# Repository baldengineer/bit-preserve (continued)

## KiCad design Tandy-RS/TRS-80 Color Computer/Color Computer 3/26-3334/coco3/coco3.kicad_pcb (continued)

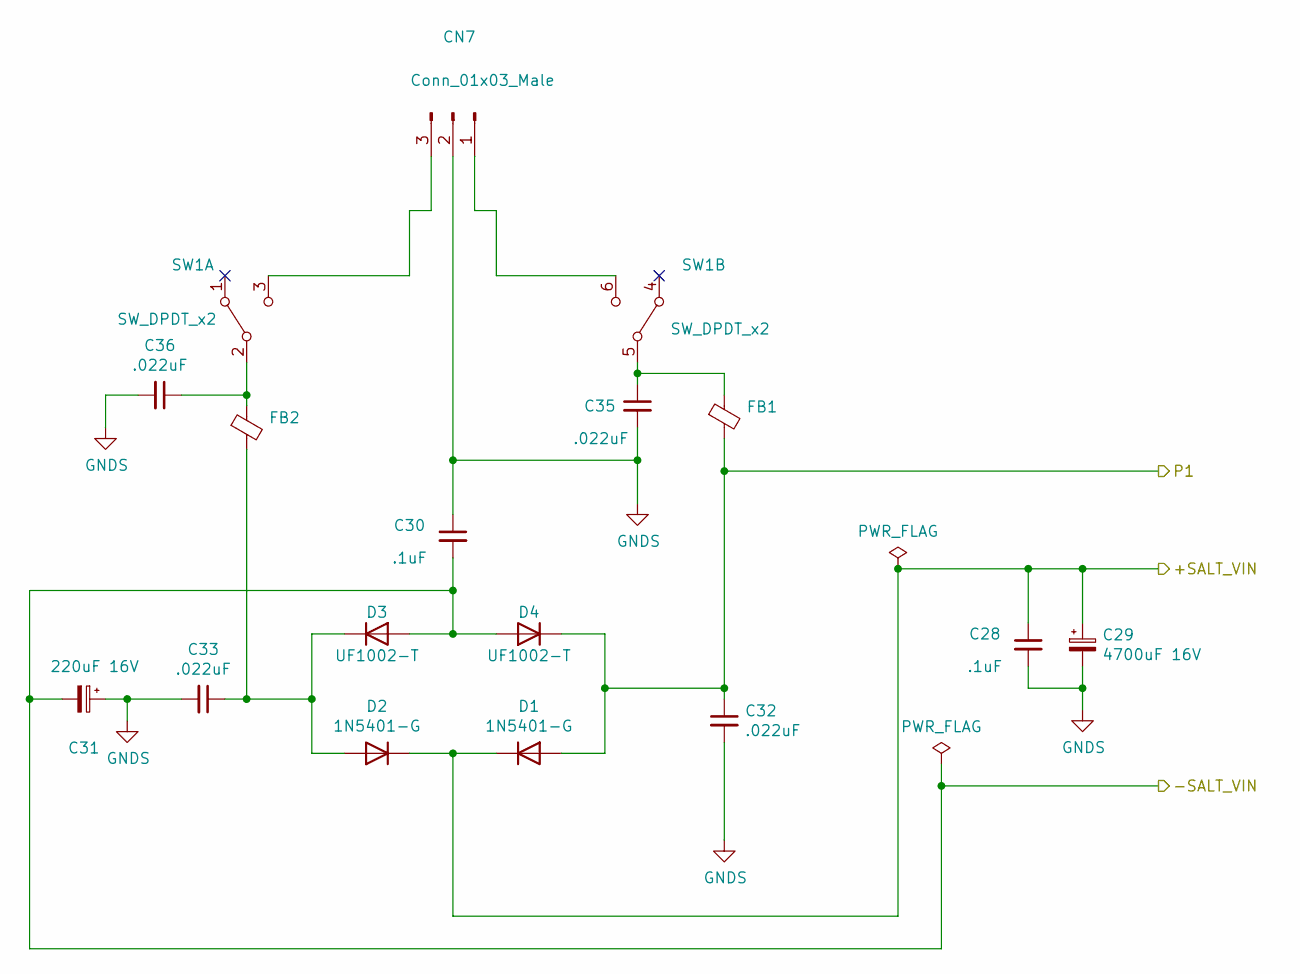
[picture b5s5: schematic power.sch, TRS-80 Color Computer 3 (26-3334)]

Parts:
C28, C30: .1uF; C_Disc_D4.7mm_W2.5mm_P5.00mm; Manufacturer part# FG28C0G1H103JNT06
C29: 4700uF 16V; CP_Radial_D12.5mm_P5.00mm; Manufacturer part# 16PK4700MEFC12.5X25
C31: 220uF 16V; CP_Radial_D8.0mm_P5.00mm; Manufacturer part# URS1C221MPD1TA
C32, C33, C35, C36: .022uF; C_Disc_D8.0mm_W2.5mm_P5.00mm; Manufacturer part# C317C223M5U5TA7301
CN7: Conn_01x03_Male; Molex_KK-396_A-41791-0003_1x03_P3.96mm_Vertical; Manufacturer part# 0009652038
D1, D2: 1N5401-G; D_DO-201AD_P15.24mm_Horizontal; Manufacturer part# 1N5401
D3, D4: UF1002-T; D_DO-41_SOD81_P10.16mm_Horizontal; Manufacturer part# UF1002-T
FB1, FB2: FB_28L0138-10R-10; Manufacturer part# 28L0138-10R-10
SW1: SW_DPDT_x2; F2UEE; Manufacturer part# F2UEE

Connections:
/peripherals/+SALT_VIN: C28.1, C29.1, D1.1 (K), D2.1 (K); also elsewhere on the board
/peripherals/-SALT_VIN: C30.2, C31.2, D3.2 (A), D4.2 (A); also elsewhere on the board
/power/P1: C32.1, D1.2 (A), D4.1 (K), FB1.2; also elsewhere on the board
GNDS: C28.2, C29.2, C30.1, C31.1, C32.2, C33.2, C35.2, C36.2, CN7.2; also elsewhere on the board
unnamed: C33.1, D2.2 (A), D3.1 (K), FB2.2
unnamed: C35.1, FB1.1, SW1.5 (B)
unnamed: C36.1, FB2.1, SW1.2 (B)
unnamed: CN7.1, SW1.6 (C)
unnamed: CN7.3, SW1.3 (C)

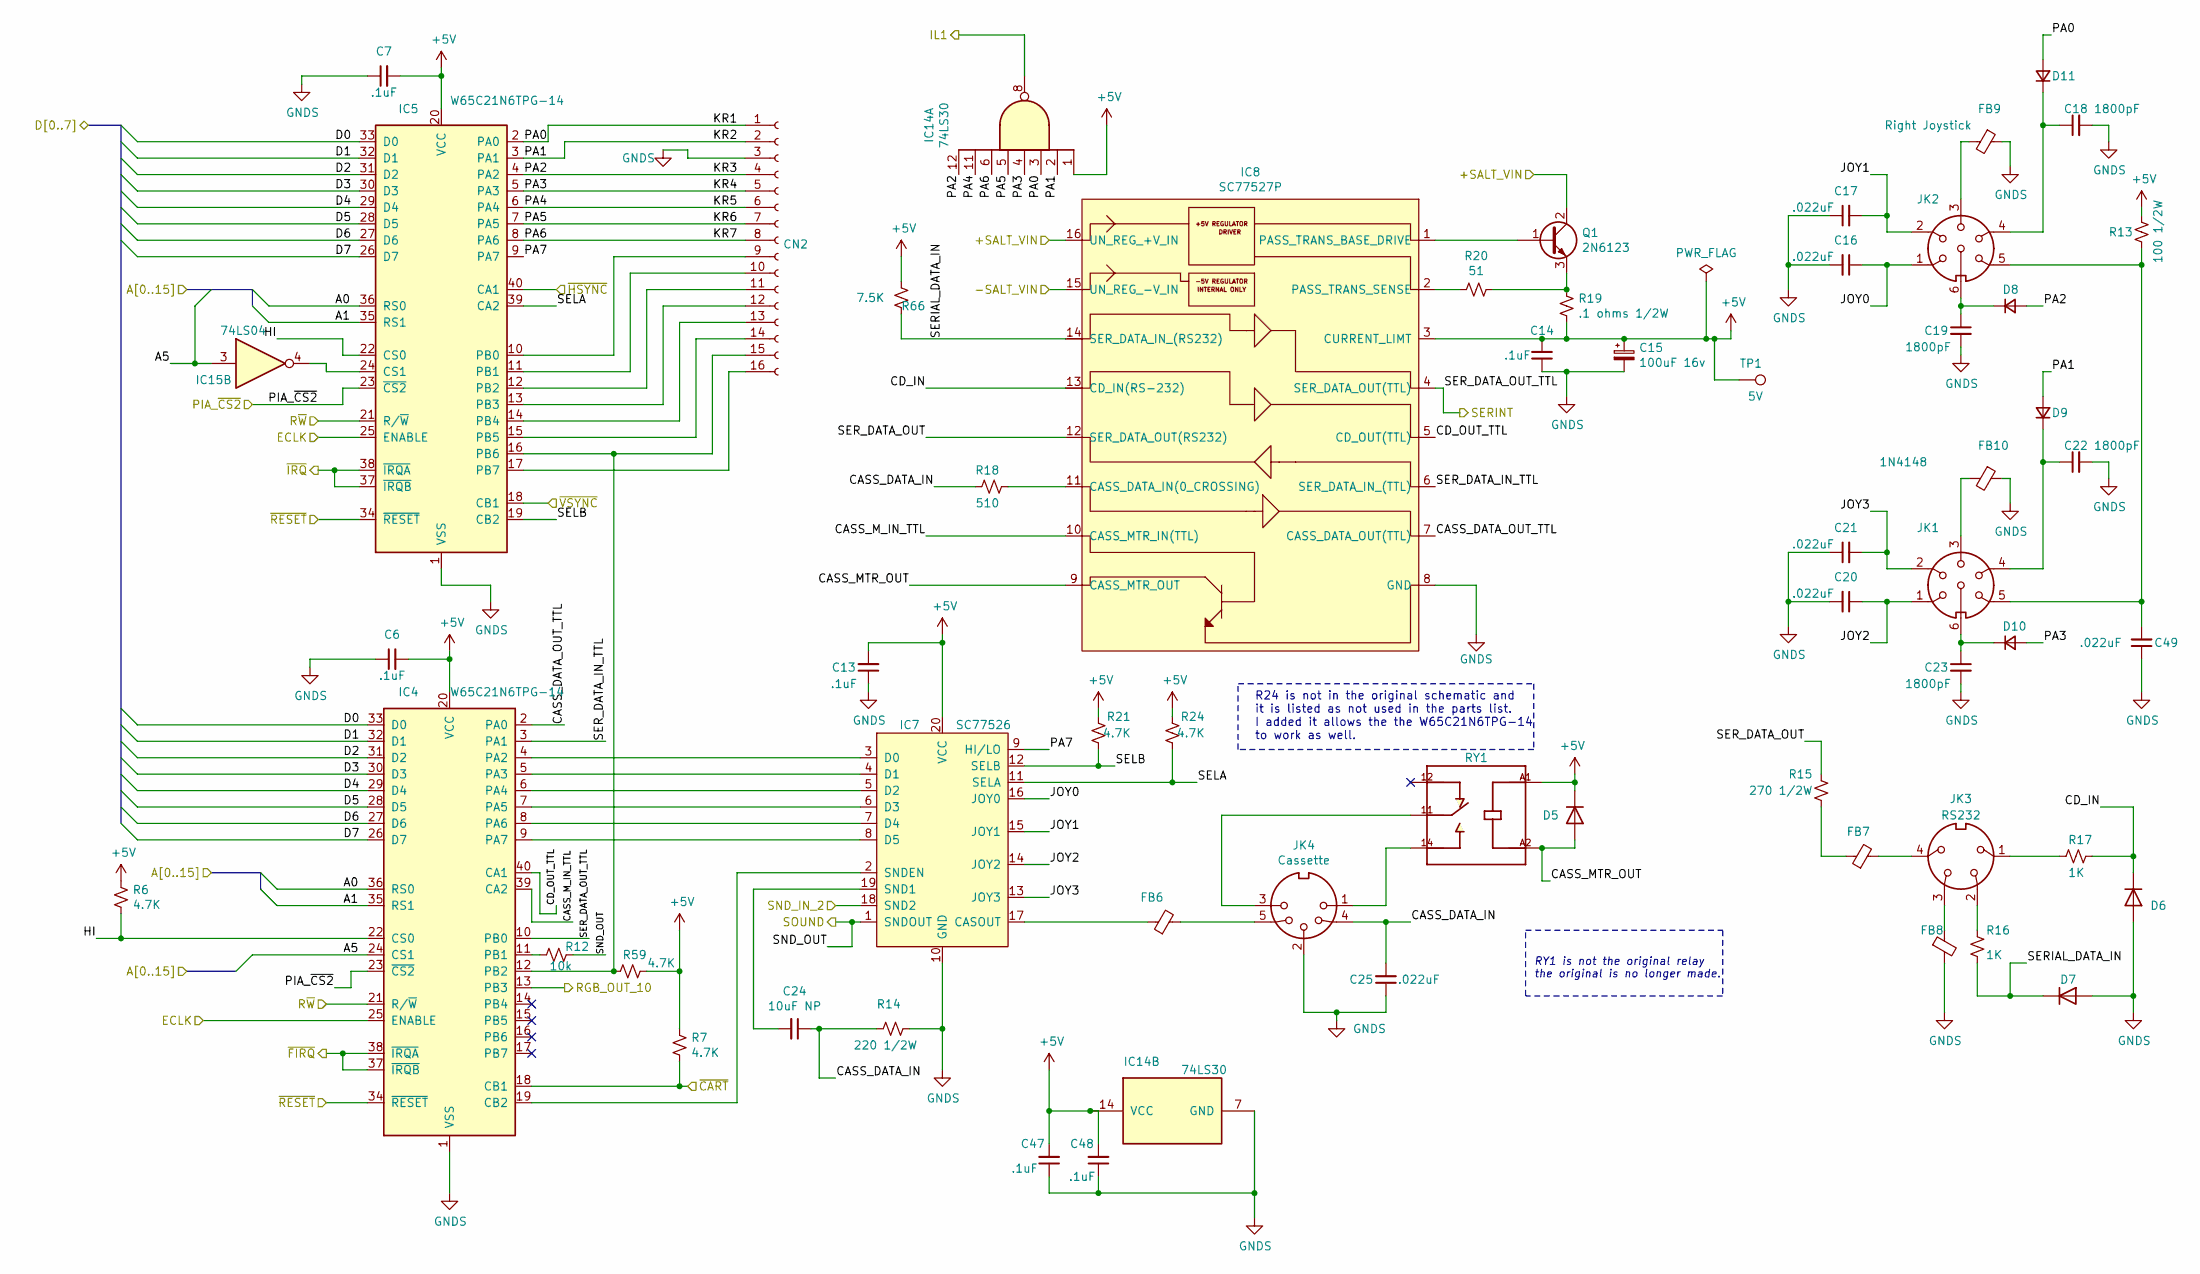
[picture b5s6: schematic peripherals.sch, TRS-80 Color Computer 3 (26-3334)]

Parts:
C6, C7, C13, C14, C47, C48: .1uF; C_Disc_D4.7mm_W2.5mm_P5.00mm; Manufacturer part# FG28C0G1H103JNT06
C15: 100uF 16v; CP_Radial_D8.0mm_P5.00mm; Manufacturer part# UST1C101MDD1TA
C16, C17, C20, C21, C25, C49: .022uF; C_Disc_D8.0mm_W2.5mm_P5.00mm; Manufacturer part# C317C223M5U5TA7301
C18, C19, C22, C23: 1800pF; C_Disc_D4.7mm_W2.5mm_P5.00mm; Manufacturer part# FA28C0G1H182JNU06
C24: 10uF NP; C_Radial_D6.3mm_H5.0mm_P2.50mm; Manufacturer part# UVP1E100MDD1TD
CN2: Conn_01x16_Female; PinHeader_1x16_P2.54mm_Vertical; Manufacturer part# 6-520415-6
D5: 1N4148; D_DO-35_SOD27_P7.62mm_Horizontal; Manufacturer part# 1N4148
D6, D7: 1N5228B-TAP; D_DO-35_SOD27_P7.62mm_Horizontal; Manufacturer part# 1N5228B-TAP
D8, D9, D10, D11: 1N4148; CUI_SDS-60J; Manufacturer part# DIODE GEN PURP 100V 200MA DO35
FB6, FB7, FB8, FB9, FB10: FB_28L0138-10R-10; Manufacturer part# 28L0138-10R-10
IC4, IC5: W65C21N6TPG-14; DIP-40_W15.24mm_Socket; Manufacturer part# W65C21N6TPG-14
IC7: SC77526; DIP-20_W7.62mm_Socket; Manufacturer part# 243-20-1-03
IC8: SC77527P; DIP-16_W7.62mm_Socket; Manufacturer part# 1-2199298-4
IC14: 74LS30; DIP-14_W7.62mm_Socket; Manufacturer part# SN74LS30N
IC15: 74LS04; DIP-14_W7.62mm_Socket; Manufacturer part# SN74LS04N
JK1: 1N4148; CUI_SDS-60J; Manufacturer part# 1N4148
JK2: Right Joystick; CUI_SDS-60J; Manufacturer part# SDS-60J
JK3: RS232; CUI_SDS-40J; Manufacturer part# SDS-40J
JK4: Cassette; CUI_SDS-50J; Manufacturer part# SDS-50J
Q1: 2N6123; TO-220-3_Horizontal_TabDown; Manufacturer part# 2N6123 PBFREE
R6, R7, R21, R24, R59: 4.7K; R_Axial_DIN0207_L6.3mm_D2.5mm_P10.16mm_Horizontal; Manufacturer part# Stackpole Electronics Inc
R12: 10k; R_Axial_DIN0207_L6.3mm_D2.5mm_P10.16mm_Horizontal; Manufacturer part# CF14JT10K0
R13: 100 1/2W; R_Axial_DIN0411_L9.9mm_D3.6mm_P12.70mm_Horizontal; Manufacturer part# CF12JT100R
R14: 220 1/2W; R_Axial_DIN0411_L9.9mm_D3.6mm_P12.70mm_Horizontal; Manufacturer part# CF12JT220R
R15: 270 1/2W; R_Axial_DIN0204_L3.6mm_D1.6mm_P7.62mm_Horizontal; Manufacturer part# SFR16S0002700JA500
R16, R17: 1K; R_Axial_DIN0207_L6.3mm_D2.5mm_P10.16mm_Horizontal; Manufacturer part# CF14JT1K00
R18: 510; R_Axial_DIN0207_L6.3mm_D2.5mm_P10.16mm_Horizontal; Manufacturer part# CF14JT510R
R19: .1 ohms 1/2W; R_Axial_DIN0411_L9.9mm_D3.6mm_P15.24mm_Horizontal; Manufacturer part# LR1LJR10
R20: 51; R_Axial_DIN0207_L6.3mm_D2.5mm_P10.16mm_Horizontal; Manufacturer part# CF1/4CT52R510J
R66: 7.5K; R_Axial_DIN0207_L6.3mm_D2.5mm_P10.16mm_Horizontal; Manufacturer part# RNF14FTD7K50
RY1: J0971CS5VDC.45; RELAY_J0971CS5VDC.45; Manufacturer part# J0971CS5VDC.45
TP1: 5V; TestPoint_Pad_3.0x3.0mm

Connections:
+5V: C6.2, C7.2, C13.2, C14.2, C15.1, C47.2, C48.2, D5.1 (K), IC4.20 (VCC), IC5.20 (VCC), IC7.20 (VCC), IC8.3 (CURRENT_LIMT), IC14.1, IC14.14 (VCC), R6.1, R7.1, R13.1, R19.1, R21.2, R24.2, R59.1, R66.2, RY1.A1, TP1.1; also elsewhere on the board
/A0: IC4.36 (RS0), IC5.36 (RS0); also elsewhere on the board
/A1: IC4.35 (RS1), IC5.35 (RS1); also elsewhere on the board
/A5: IC4.24 (CS1), IC15.3; also elsewhere on the board
/D0: IC4.33 (D0), IC5.33 (D0); also elsewhere on the board
/D1: IC4.32 (D1), IC5.32 (D1); also elsewhere on the board
/D2: IC4.31 (D2), IC5.31 (D2); also elsewhere on the board
/D3: IC4.30 (D3), IC5.30 (D3); also elsewhere on the board
/D4: IC4.29 (D4), IC5.29 (D4); also elsewhere on the board
/D5: IC4.28 (D5), IC5.28 (D5); also elsewhere on the board
/D6: IC4.27 (D6), IC5.27 (D6); also elsewhere on the board
/D7: IC4.26 (D7), IC5.26 (D7); also elsewhere on the board
/ECLK: IC4.25 (ENABLE), IC5.25 (ENABLE); also elsewhere on the board
/R~W: IC4.21 (R/~W), IC5.21 (R/~W); also elsewhere on the board
/SND_IN_2: IC7.18 (SND2); also elsewhere on the board
/gime/IL1: IC14.8; also elsewhere on the board
/gime/PIA_~CS2: IC4.23 (~CS2), IC5.23 (~CS2); also elsewhere on the board
/gime/SERINT: IC4.10 (PB0), IC8.4 (SER_DATA_OUT(TTL)); also elsewhere on the board
/gime/~HSYNC: IC5.40 (CA1); also elsewhere on the board
/gime/~VSYNC: IC5.18 (CB1); also elsewhere on the board
/peripherals/+SALT_VIN: IC8.16 (UN_REG_+V_IN), Q1.2 (C); also elsewhere on the board
/peripherals/-SALT_VIN: IC8.15 (UN_REG_-V_IN); also elsewhere on the board
/peripherals/CASS_DATA_IN: C24.1, C25.2, JK4.4, R14.2, R18.1
/peripherals/CASS_DATA_OUT_TTL: IC4.2 (PA0), IC8.7 (CASS_DATA_OUT(TTL))
/peripherals/CASS_MTR_OUT: D5.2 (A), IC8.9 (CASS_MTR_OUT), RY1.A2
/peripherals/CASS_M_IN_TTL: IC4.39 (CA2), IC8.10 (CASS_MTR_IN(TTL))
/peripherals/CD_IN: D6.1 (K), IC8.13 (CD_IN(RS-232)), R17.1
/peripherals/CD_OUT_TTL: IC4.40 (CA1), IC8.5 (CD_OUT(TTL))
/peripherals/HI: IC4.22 (CS0), IC5.22 (CS0), R6.2
/peripherals/JOY0: C16.1, IC7.16 (JOY0), JK2.1
/peripherals/JOY1: C17.2, IC7.15 (JOY1), JK2.2
/peripherals/JOY2: C20.1, IC7.14 (JOY2), JK1.1
/peripherals/JOY3: C21.2, IC7.13 (JOY3), JK1.2
/peripherals/KR1: CN2.1, D11.2 (A), IC5.2 (PA0), IC14.3
/peripherals/KR2: CN2.2, D9.2 (A), IC5.3 (PA1), IC14.2
/peripherals/KR3: CN2.4, D8.2 (A), IC5.4 (PA2), IC14.12
/peripherals/KR4: CN2.5, D10.2 (A), IC5.5 (PA3), IC14.4
/peripherals/KR5: CN2.6, IC5.6 (PA4), IC14.11
/peripherals/KR6: CN2.7, IC5.7 (PA5), IC14.5
/peripherals/KR7: CN2.8, IC5.8 (PA6), IC14.6
/peripherals/PA7: IC5.9 (PA7), IC7.9 (HI/LO)
/peripherals/RGB_OUT_10: IC4.13 (PB3); also elsewhere on the board
/peripherals/SELA: IC5.39 (CA2), IC7.11 (SELA), R24.1
/peripherals/SELB: IC5.19 (CB2), IC7.12 (SELB), R21.1
/peripherals/SERIAL_DATA_IN: D7.1 (K), IC8.14 (SER_DATA_IN_(RS232)), R16.2, R66.1
/peripherals/SER_DATA_IN_TTL: IC4.3 (PA1), IC8.6 (SER_DATA_IN_(TTL))
/peripherals/SER_DATA_OUT: IC8.12 (SER_DATA_OUT(RS232)), R15.2
/peripherals/SOUND: IC7.1 (SNDOUT), R12.1; also elsewhere on the board
/~CART: IC4.18 (CB1), R7.2; also elsewhere on the board
/~FIRQ: IC4.37 (~IRQB), IC4.38 (~IRQA); also elsewhere on the board
/~IRQ: IC5.37 (~IRQB), IC5.38 (~IRQA); also elsewhere on the board
/~RESET: IC4.34 (~RESET), IC5.34 (~RESET); also elsewhere on the board
GNDS: C6.1, C7.1, C13.1, C14.1, C15.2, C16.2, C17.1, C18.2, C19.2, C20.2, C21.1, C22.2, C23.2, C25.1, C47.1, C48.1, C49.1, CN2.3, D6.2 (A), D7.2 (A), FB8.2, FB9.1, FB10.1, IC4.1 (VSS), IC5.1 (VSS), IC7.10 (GND), IC8.8 (GND), IC14.7 (GND), JK4.2, R14.1; also elsewhere on the board
unnamed: C18.1, D11.1 (K), JK2.4
unnamed: C19.1, D8.1 (K), JK2.6
unnamed: C22.1, D9.1 (K), JK1.4
unnamed: C23.1, D10.1 (K), JK1.6
unnamed: C24.2, IC7.19 (SND1)
unnamed: C49.2, JK1.5, JK2.5, R13.2
unnamed: CN2.9, IC5.10 (PB0)
unnamed: CN2.10, IC5.11 (PB1)
unnamed: CN2.11, IC5.12 (PB2)
unnamed: CN2.12, IC5.13 (PB3)
unnamed: CN2.13, IC5.14 (PB4)
unnamed: CN2.14, IC5.15 (PB5)
unnamed: CN2.15, IC4.12 (PB2), IC5.16 (PB6), R59.2
unnamed: CN2.16, IC5.17 (PB7)
unnamed: FB6.1, IC7.17 (CASOUT)
unnamed: FB6.2, JK4.5
unnamed: FB7.1, R15.1
unnamed: FB7.2, JK3.4
unnamed: FB8.1, JK3.3
unnamed: FB9.2, JK2.3
unnamed: FB10.2, JK1.3
unnamed: IC4.4 (PA2), IC7.3 (D0)
unnamed: IC4.5 (PA3), IC7.4 (D1)
unnamed: IC4.6 (PA4), IC7.5 (D2)
unnamed: IC4.7 (PA5), IC7.6 (D3)
unnamed: IC4.8 (PA6), IC7.7 (D4)
unnamed: IC4.9 (PA7), IC7.8 (D5)
unnamed: IC4.11 (PB1), R12.2
unnamed: IC4.19 (CB2), IC7.2 (SNDEN)
unnamed: IC8.1 (PASS_TRANS_BASE_DRIVE), Q1.1 (B)
unnamed: IC8.2 (PASS_TRANS_SENSE), R20.2
unnamed: IC8.11 (CASS_DATA_IN(0_CROSSING)), R18.2
unnamed: IC5.24 (CS1), IC15.4
unnamed: JK3.1, R17.2
unnamed: JK3.2, R16.1
unnamed: JK4.1, RY1.14
unnamed: JK4.3, RY1.11
unnamed: Q1.3 (E), R19.2, R20.1

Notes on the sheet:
RY1 is not the original relay the original is no longer made.
R24 is not in the original schematic and it is listed as not used in the parts list. I added it allows the the W65C21N6TPG-14 to work as well.

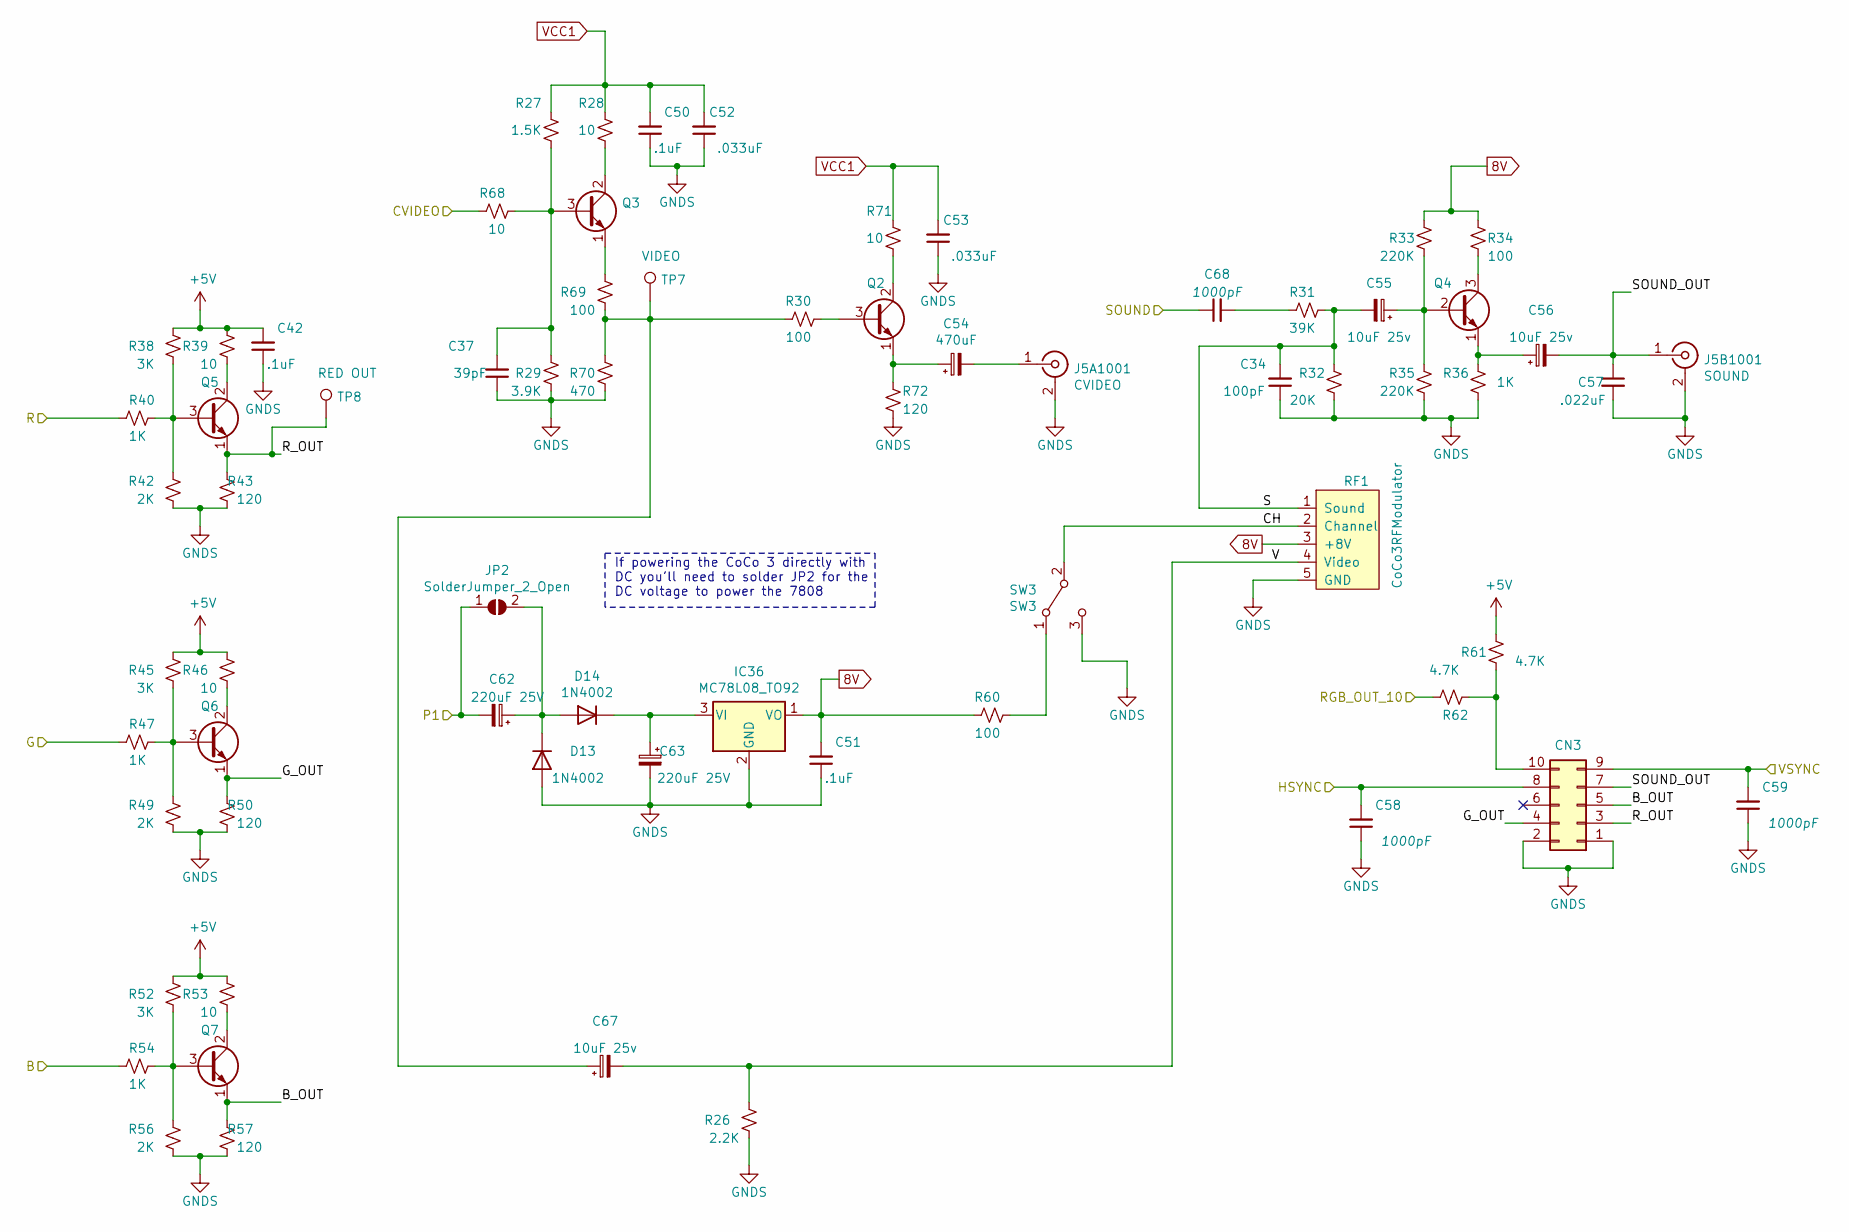
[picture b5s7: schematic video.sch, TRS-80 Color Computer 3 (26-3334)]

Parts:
C34: 100pF; C_Disc_D4.3mm_W1.9mm_P5.00mm; Manufacturer part# K101J15C0GF5TH5
C37: 39pF; C_Disc_D4.7mm_W2.5mm_P5.00mm; Manufacturer part# K390J15C0GF5TL2
C42, C50, C51: .1uF; C_Disc_D4.7mm_W2.5mm_P5.00mm; Manufacturer part# FG28C0G1H103JNT06
C52, C53: .033uF; C_Axial_L5.1mm_D3.1mm_P10.00mm_Horizontal; Manufacturer part# C410C333K5R5TA7200
C54: 470uF; CP_Radial_D8.0mm_P3.50mm; Manufacturer part# ECA-1CM471
C55, C56, C67: 10uF 25v; CP_Radial_D5.0mm_P2.00mm; Manufacturer part# UPW1E100MDD
C57: .022uF; C_Axial_L5.1mm_D3.1mm_P10.00mm_Horizontal; Manufacturer part# C410C223K5R5TA7200
C58, C59, C68: 1000pF; C_Disc_D4.7mm_W2.5mm_P5.00mm; Manufacturer part# K102K10X7RF5UH5
C62, C63: 220uF 25V; CP_Radial_D8.0mm_P3.50mm; Manufacturer part# ECA-1EM221
CN3: Conn_02x05_Odd_Even; PinHeader_2x05_P2.54mm_Vertical; Manufacturer part# PRPC005DAAN-RC
D13, D14: 1N4002; D_DO-41_SOD81_P10.16mm_Horizontal; Manufacturer part# 1N4002-TP
IC36: MC78L08_TO92; TO-92_Inline; Manufacturer part# UA78L08ACLPRE3
J5A1001: CVIDEO; KLPX-0848A-2-R; Manufacturer part# KLPX-0848A-2-R
J5B1001: SOUND; KLPX-0848A-2-R; Manufacturer part# KLPX-0848A-2-W
JP2: SolderJumper_2_Open; SolderJumper-2_P1.3mm_Open_Pad1.0x1.5mm
Q2, Q3, Q5, Q6, Q7: 2SC1815; TO-92L_Inline; Manufacturer part# 2SC1815 PBFREE
Q4: BCX38C; TO-92L_Inline; Manufacturer part# BCX38C
R26: 2.2K; R_Axial_DIN0207_L6.3mm_D2.5mm_P10.16mm_Horizontal; Manufacturer part# CF14JT2K20
R27: 1.5K; R_Axial_DIN0207_L6.3mm_D2.5mm_P10.16mm_Horizontal; Manufacturer part# RNF14FTD1K50
R28, R39, R46, R53, R68, R71: 10; R_Axial_DIN0207_L6.3mm_D2.5mm_P10.16mm_Horizontal; Manufacturer part# CFR-25JB-52-10R
R29: 3.9K; R_Axial_DIN0207_L6.3mm_D2.5mm_P10.16mm_Horizontal; Manufacturer part# CF14JT3K90
R30, R34, R60, R69: 100; R_Axial_DIN0207_L6.3mm_D2.5mm_P10.16mm_Horizontal; Manufacturer part# CF14JT100R
R31: 39K; R_Axial_DIN0207_L6.3mm_D2.5mm_P10.16mm_Horizontal; Manufacturer part# CFR-25JB-52-39K
R32: 20K; R_Axial_DIN0207_L6.3mm_D2.5mm_P10.16mm_Horizontal; Manufacturer part# CFR-25JB-52-20K
R33, R35: 220K; R_Axial_DIN0207_L6.3mm_D2.5mm_P10.16mm_Horizontal; Manufacturer part# CF14JT220K
R36, R40, R47, R54: 1K; R_Axial_DIN0207_L6.3mm_D2.5mm_P10.16mm_Horizontal; Manufacturer part# CF14JT1K00
R38, R45, R52: 3K; R_Axial_DIN0207_L6.3mm_D2.5mm_P10.16mm_Horizontal; Manufacturer part# CFR-25JB-52-3K
R42, R49, R56: 2K; R_Axial_DIN0207_L6.3mm_D2.5mm_P10.16mm_Horizontal; Manufacturer part# RNF14FTD2K00
R43, R50, R57, R72: 120; R_Axial_DIN0207_L6.3mm_D2.5mm_P10.16mm_Horizontal; Manufacturer part# CF14JT120R
R61, R62: 4.7K; R_Axial_DIN0207_L6.3mm_D2.5mm_P10.16mm_Horizontal; Manufacturer part# Stackpole Electronics Inc
R70: 470; R_Axial_DIN0207_L6.3mm_D2.5mm_P10.16mm_Horizontal; Manufacturer part# CF14JT470R
RF1: CoCo3RFModulator; CoCo 3 RF Modulator
SW3: SW3; SW_EG1213; Manufacturer part# EG1213
TP7: VIDEO; TestPoint_Pad_3.0x3.0mm
TP8: RED OUT; TestPoint_Pad_3.0x3.0mm

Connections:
8V: C51.2, IC36.1 (VO), R33.1, R34.2, R60.1, RF1.3 (+8V)
+5V: C42.2, R38.2, R39.2, R45.2, R46.2, R52.2, R53.2, R61.1; also elsewhere on the board
/gime/B: R54.2; also elsewhere on the board
/gime/CVIDEO: R68.1; also elsewhere on the board
/gime/G: R47.2; also elsewhere on the board
/gime/HSYNC: C58.2, CN3.8; also elsewhere on the board
/gime/R: R40.2; also elsewhere on the board
/gime/VSYNC: C59.2, CN3.9; also elsewhere on the board
/peripherals/RGB_OUT_10: R62.1; also elsewhere on the board
/peripherals/SOUND: C68.1; also elsewhere on the board
/power/P1: C62.2, JP2.1 (A); also elsewhere on the board
/video/B_OUT: CN3.5, Q7.1 (E), R57.2
/video/CH: RF1.2 (Channel), SW3.2 (B)
/video/G_OUT: CN3.4, Q6.1 (E), R50.2
/video/R_OUT: CN3.3, Q5.1 (E), R43.2, TP8.1
/video/S: C34.2, C55.2, R31.2, R32.1, RF1.1 (Sound)
/video/SOUND_OUT: C56.2, C57.1, CN3.7, J5B1001.1 (In)
/video/V: C67.2, R26.2, RF1.4 (Video)
GNDS: C34.1, C37.1, C42.1, C50.1, C51.1, C52.1, C53.1, C57.2, C58.1, C59.1, C63.2, CN3.1, CN3.2, D13.2 (A), IC36.2 (GND), J5A1001.2 (Ext), J5B1001.2 (Ext), R26.1, R29.1, R32.2, R35.2, R36.2, R42.1, R43.1, R49.1, R50.1, R56.1, R57.1, R70.1, R72.1, RF1.5 (GND), SW3.3 (C); also elsewhere on the board
unnamed: C37.2, Q3.3 (B), R27.1, R29.2, R68.2
unnamed: C54.1, Q2.1 (E), R72.2
unnamed: C54.2, J5A1001.1 (In)
unnamed: C55.1, Q4.2 (B), R33.2, R35.1
unnamed: C56.1, Q4.1 (E), R36.1
unnamed: C62.1, D13.1 (K), D14.2 (A), JP2.2 (B)
unnamed: C63.1, D14.1 (K), IC36.3 (VI)
unnamed: C67.1, R30.1, R69.1, R70.2, TP7.1
unnamed: C68.2, R31.1
unnamed: CN3.10, R61.2, R62.2
unnamed: Q2.2 (C), R71.1
unnamed: Q2.3 (B), R30.2
unnamed: Q3.1 (E), R69.2
unnamed: Q3.2 (C), R28.1
unnamed: Q4.3 (C), R34.1
unnamed: Q5.2 (C), R39.1
unnamed: Q5.3 (B), R38.1, R40.1, R42.2
unnamed: Q6.2 (C), R46.1
unnamed: Q6.3 (B), R45.1, R47.1, R49.2
unnamed: Q7.2 (C), R53.1
unnamed: Q7.3 (B), R52.1, R54.1, R56.2
unnamed: R60.2, SW3.1 (A)
VCC1: C50.2, C52.2, C53.2, R27.2, R28.2, R71.2; also elsewhere on the board

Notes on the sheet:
If powering the CoCo 3 directly with DC you'll need to solder JP2 for the DC voltage to power the 7808

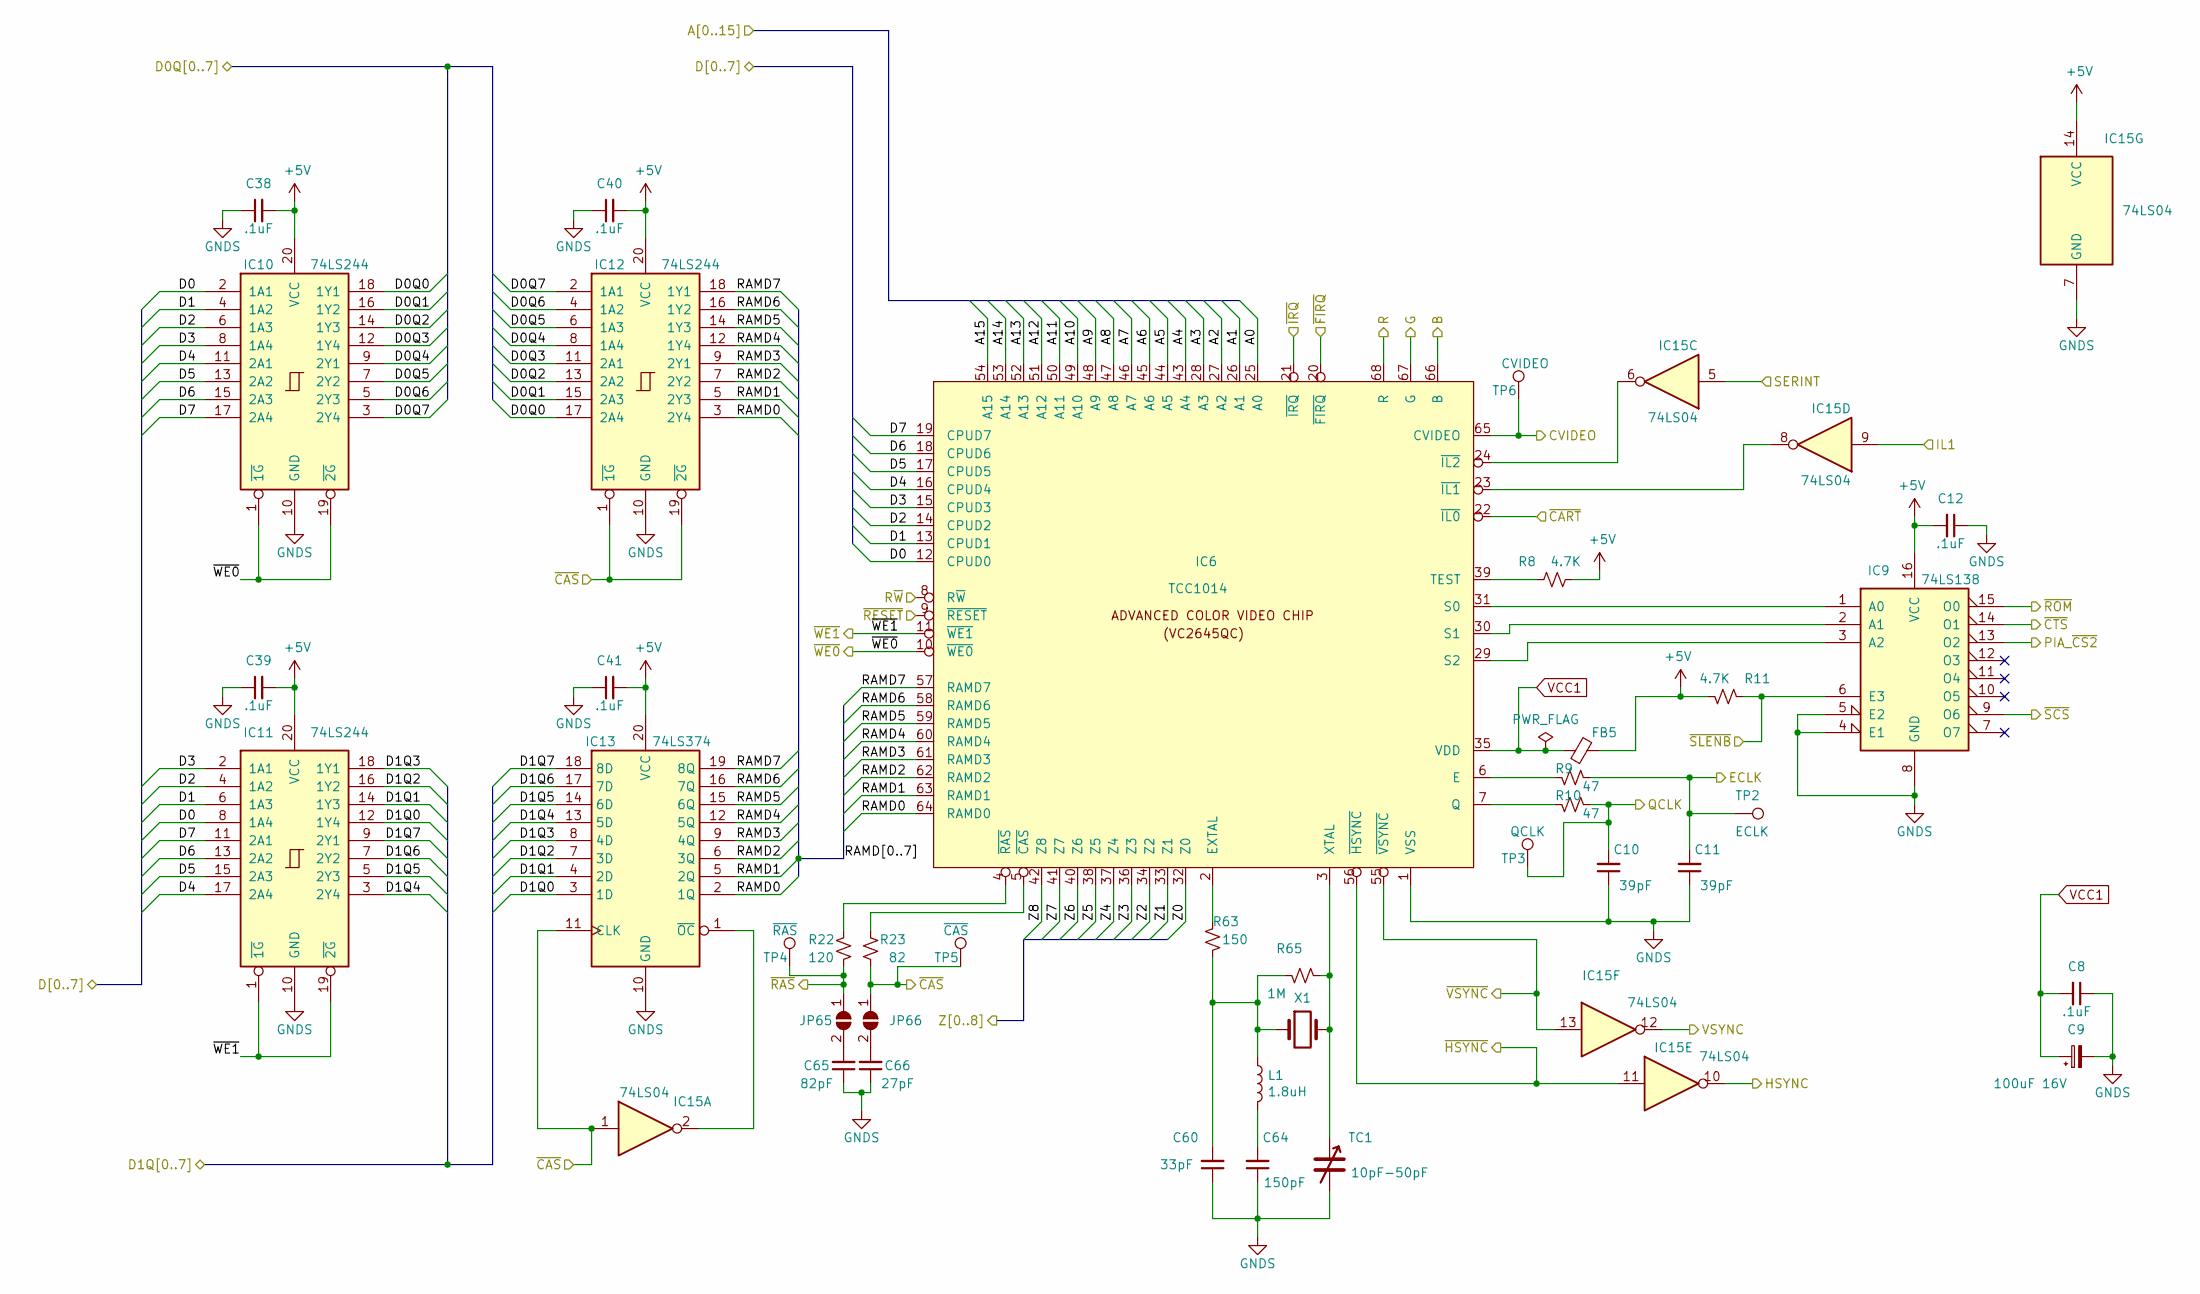
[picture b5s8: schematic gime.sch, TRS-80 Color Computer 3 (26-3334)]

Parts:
C8, C12, C38, C39, C40, C41: .1uF; C_Disc_D4.7mm_W2.5mm_P5.00mm; Manufacturer part# FG28C0G1H103JNT06
C9: 100uF 16V; CP_Radial_D5.0mm_P2.00mm; Manufacturer part# 16ZLH100MEFC5X11
C10, C11: 39pF; C_Disc_D4.7mm_W2.5mm_P5.00mm; Manufacturer part# K390J15C0GF5TL2
C60: 33pF; C_Rect_L7.2mm_W3.0mm_P5.00mm_FKS2_FKP2_MKS2_MKP2; Manufacturer part# FA28NP01H330JNU06
C64: 150pF; C_Rect_L7.2mm_W2.5mm_P5.00mm_FKS2_FKP2_MKS2_MKP2; Manufacturer part# FA28C0G2E151JNU06
C65: 82pF; C_Rect_L7.2mm_W3.0mm_P5.00mm_FKS2_FKP2_MKS2_MKP2; Manufacturer part# K820J15C0GF5TH5
C66: 27pF; C_Rect_L7.2mm_W3.0mm_P5.00mm_FKS2_FKP2_MKS2_MKP2; Manufacturer part# K270J15C0GF5TH5
FB5: FB_28L0138-10R-10; Manufacturer part# 28L0138-10R-10
IC6: TCC1014; PLCC-68_THT-Socket; Manufacturer part# A-CCS 068-G-T
IC9: 74LS138; DIP-16_W7.62mm_Socket; Manufacturer part# SN74LS138N
IC10, IC11, IC12: 74LS244; DIP-20_W7.62mm_Socket; Manufacturer part# SN74LS244N
IC13: 74LS374; DIP-20_W7.62mm_Socket; Manufacturer part# SN74ALS374AN
IC15: 74LS04; DIP-14_W7.62mm_Socket; Manufacturer part# SN74LS04N
JP65, JP66: SolderJumper_2_Open; SolderJumper-2_P1.3mm_Open_RoundedPad1.0x1.5mm
L1: 1.8uH; L_Axial_L9.5mm_D4.0mm_P12.70mm_Horizontal_Fastron_SMCC; Manufacturer part# 1537-18K
R8, R11: 4.7K; R_Axial_DIN0207_L6.3mm_D2.5mm_P10.16mm_Horizontal; Manufacturer part# Stackpole Electronics Inc
R9, R10: 47; R_Axial_DIN0309_L9.0mm_D3.2mm_P12.70mm_Horizontal; Manufacturer part# CF12JT47R0
R22: 120; R_Axial_DIN0207_L6.3mm_D2.5mm_P10.16mm_Horizontal; Manufacturer part# CF14JT120R
R23: 82; R_Axial_DIN0207_L6.3mm_D2.5mm_P10.16mm_Horizontal; Manufacturer part# CF1/4CT52R820J
R63: 150; R_Axial_DIN0309_L9.0mm_D3.2mm_P12.70mm_Horizontal; Manufacturer part# CF12JT150R
R65: 1M; R_Axial_DIN0207_L6.3mm_D2.5mm_P10.16mm_Horizontal; Manufacturer part# RNF14FTD1M00
TC1: 10pF-50pF; C_Rect_L7.2mm_W7.2mm_P5.00mm_FKS2_FKP2_MKS2_MKP2; Manufacturer part# GKG60015
TP2: ECLK; TestPoint_Pad_3.0x3.0mm
TP3: QCLK; TestPoint_Pad_3.0x3.0mm
TP4: ~RAS; TestPoint_Pad_3.0x3.0mm
TP5: ~CAS; TestPoint_Pad_3.0x3.0mm
TP6: CVIDEO; TestPoint_Pad_3.0x3.0mm
X1: 28.63636 MHz; XTAL_ECS-286.3-20-46X; Manufacturer part# ECS-286.3-20-46X

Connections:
+5V: C12.2, C38.2, C39.2, C40.2, C41.2, FB5.2, IC9.16 (VCC), IC10.20 (VCC), IC11.20 (VCC), IC12.20 (VCC), IC13.20 (VCC), IC15.14 (VCC), R8.2, R11.2; also elsewhere on the board
/A0: IC6.25 (A0); also elsewhere on the board
/A1: IC6.26 (A1); also elsewhere on the board
/A2: IC6.27 (A2); also elsewhere on the board
/A3: IC6.28 (A3); also elsewhere on the board
/A4: IC6.43 (A4); also elsewhere on the board
/A5: IC6.44 (A5); also elsewhere on the board
/A6: IC6.45 (A6); also elsewhere on the board
/A7: IC6.46 (A7); also elsewhere on the board
/A8: IC6.47 (A8); also elsewhere on the board
/A9: IC6.48 (A9); also elsewhere on the board
/A10: IC6.49 (A10); also elsewhere on the board
/A11: IC6.50 (A11); also elsewhere on the board
/A12: IC6.51 (A12); also elsewhere on the board
/A13: IC6.52 (A13); also elsewhere on the board
/A14: IC6.53 (A14); also elsewhere on the board
/A15: IC6.54 (A15); also elsewhere on the board
/D0: IC6.12 (CPUD0), IC10.2 (1A1), IC11.8 (1A4); also elsewhere on the board
/D1: IC6.13 (CPUD1), IC10.4 (1A2), IC11.6 (1A3); also elsewhere on the board
/D2: IC6.14 (CPUD2), IC10.6 (1A3), IC11.4 (1A2); also elsewhere on the board
/D3: IC6.15 (CPUD3), IC10.8 (1A4), IC11.2 (1A1); also elsewhere on the board
/D4: IC6.16 (CPUD4), IC10.11 (2A1), IC11.17 (2A4); also elsewhere on the board
/D5: IC6.17 (CPUD5), IC10.13 (2A2), IC11.15 (2A3); also elsewhere on the board
/D6: IC6.18 (CPUD6), IC10.15 (2A3), IC11.13 (2A2); also elsewhere on the board
/D7: IC6.19 (CPUD7), IC10.17 (2A4), IC11.11 (2A1); also elsewhere on the board
/ECLK: C11.2, R9.1, TP2.1; also elsewhere on the board
/QCLK: C10.2, R10.1, TP3.1; also elsewhere on the board
/R~W: IC6.8 (R~W); also elsewhere on the board
/dram/D0Q0: IC10.18 (1Y1), IC12.17 (2A4); also elsewhere on the board
/dram/D0Q1: IC10.16 (1Y2), IC12.15 (2A3); also elsewhere on the board
/dram/D0Q2: IC10.14 (1Y3), IC12.13 (2A2); also elsewhere on the board
/dram/D0Q3: IC10.12 (1Y4), IC12.11 (2A1); also elsewhere on the board
/dram/D0Q4: IC10.9 (2Y1), IC12.8 (1A4); also elsewhere on the board
/dram/D0Q5: IC10.7 (2Y2), IC12.6 (1A3); also elsewhere on the board
/dram/D0Q6: IC10.5 (2Y3), IC12.4 (1A2); also elsewhere on the board
/dram/D0Q7: IC10.3 (2Y4), IC12.2 (1A1); also elsewhere on the board
/dram/D1Q0: IC11.12 (1Y4), IC13.3 (1D); also elsewhere on the board
/dram/D1Q1: IC11.14 (1Y3), IC13.4 (2D); also elsewhere on the board
/dram/D1Q2: IC11.16 (1Y2), IC13.7 (3D); also elsewhere on the board
/dram/D1Q3: IC11.18 (1Y1), IC13.8 (4D); also elsewhere on the board
/dram/D1Q4: IC11.3 (2Y4), IC13.13 (5D); also elsewhere on the board
/dram/D1Q5: IC11.5 (2Y3), IC13.14 (6D); also elsewhere on the board
/dram/D1Q6: IC11.7 (2Y2), IC13.17 (7D); also elsewhere on the board
/dram/D1Q7: IC11.9 (2Y1), IC13.18 (8D); also elsewhere on the board
/dram/Z0: IC6.32 (Z0); also elsewhere on the board
/dram/Z1: IC6.33 (Z1); also elsewhere on the board
/dram/Z2: IC6.34 (Z2); also elsewhere on the board
/dram/Z3: IC6.36 (Z3); also elsewhere on the board
/dram/Z4: IC6.37 (Z4); also elsewhere on the board
/dram/Z5: IC6.38 (Z5); also elsewhere on the board
/dram/Z6: IC6.40 (Z6); also elsewhere on the board
/dram/Z7: IC6.41 (Z7); also elsewhere on the board
/dram/Z8: IC6.42 (Z8); also elsewhere on the board
/dram/~CAS: IC12.1 (~1G), IC12.19 (~2G), IC13.11 (CLK), IC15.1, JP66.1 (A), R23.1, TP5.1; also elsewhere on the board
/dram/~RAS: JP65.1 (A), R22.1, TP4.1; also elsewhere on the board
/dram/~WE0: IC6.10 (~WE0), IC10.1 (~1G), IC10.19 (~2G); also elsewhere on the board
/dram/~WE1: IC6.11 (~WE1), IC11.1 (~1G), IC11.19 (~2G); also elsewhere on the board
/gime/B: IC6.66 (B); also elsewhere on the board
/gime/CVIDEO: IC6.65 (CVIDEO), TP6.1; also elsewhere on the board
/gime/G: IC6.67 (G); also elsewhere on the board
/gime/HSYNC: IC15.10; also elsewhere on the board
/gime/IL1: IC15.9; also elsewhere on the board
/gime/PIA_~CS2: IC9.13 (O2); also elsewhere on the board
/gime/R: IC6.68 (R); also elsewhere on the board
/gime/RAMD0: IC6.64 (RAMD0), IC12.3 (2Y4), IC13.2 (1Q)
/gime/RAMD1: IC6.63 (RAMD1), IC12.5 (2Y3), IC13.5 (2Q)
/gime/RAMD2: IC6.62 (RAMD2), IC12.7 (2Y2), IC13.6 (3Q)
/gime/RAMD3: IC6.61 (RAMD3), IC12.9 (2Y1), IC13.9 (4Q)
/gime/RAMD4: IC6.60 (RAMD4), IC12.12 (1Y4), IC13.12 (5Q)
/gime/RAMD5: IC6.59 (RAMD5), IC12.14 (1Y3), IC13.15 (6Q)
/gime/RAMD6: IC6.58 (RAMD6), IC12.16 (1Y2), IC13.16 (7Q)
/gime/RAMD7: IC6.57 (RAMD7), IC12.18 (1Y1), IC13.19 (8Q)
/gime/SERINT: IC15.5; also elsewhere on the board
/gime/VSYNC: IC15.12; also elsewhere on the board
/gime/~HSYNC: IC6.56 (~HSYNC), IC15.11; also elsewhere on the board
/gime/~ROM: IC9.15 (O0); also elsewhere on the board
/gime/~VSYNC: IC6.55 (~VSYNC), IC15.13; also elsewhere on the board
/~CART: IC6.22 (~IL0); also elsewhere on the board
/~CTS: IC9.14 (O1); also elsewhere on the board
/~FIRQ: IC6.20 (~FIRQ); also elsewhere on the board
/~IRQ: IC6.21 (~IRQ); also elsewhere on the board
/~RESET: IC6.9 (~RESET); also elsewhere on the board
/~SCS: IC9.9 (O6); also elsewhere on the board
/~SLENB: IC9.6 (E3), R11.1; also elsewhere on the board
GNDS: C8.1, C9.2, C10.1, C11.1, C12.1, C38.1, C39.1, C40.1, C41.1, C60.1, C64.1, C65.1, C66.1, IC6.1 (VSS), IC9.4 (E1), IC9.5 (E2), IC9.8 (GND), IC10.10 (GND), IC11.10 (GND), IC12.10 (GND), IC13.10 (GND), IC15.7 (GND), TC1.2; also elsewhere on the board
unnamed: C60.2, L1.1, R63.2, R65.2, X1.1
unnamed: C64.2, L1.2
unnamed: C65.2, JP65.2 (B)
unnamed: C66.2, JP66.2 (B)
unnamed: IC6.2 (EXTAL), R63.1
unnamed: IC6.3 (XTAL), R65.1, TC1.1, X1.2
unnamed: IC6.4 (~RAS), R22.2
unnamed: IC6.5 (~CAS), R23.2
unnamed: IC6.6 (E), R9.2
unnamed: IC6.7 (Q), R10.2
unnamed: IC6.29 (S2), IC9.3 (A2)
unnamed: IC6.30 (S1), IC9.2 (A1)
unnamed: IC6.31 (S0), IC9.1 (A0)
unnamed: IC6.39 (TEST), R8.1
unnamed: IC13.1 (~OC), IC15.2
unnamed: IC6.24 (~IL2), IC15.6
unnamed: IC6.23 (~IL1), IC15.8
VCC1: C8.2, C9.1, FB5.1, IC6.35 (VDD); also elsewhere on the board
